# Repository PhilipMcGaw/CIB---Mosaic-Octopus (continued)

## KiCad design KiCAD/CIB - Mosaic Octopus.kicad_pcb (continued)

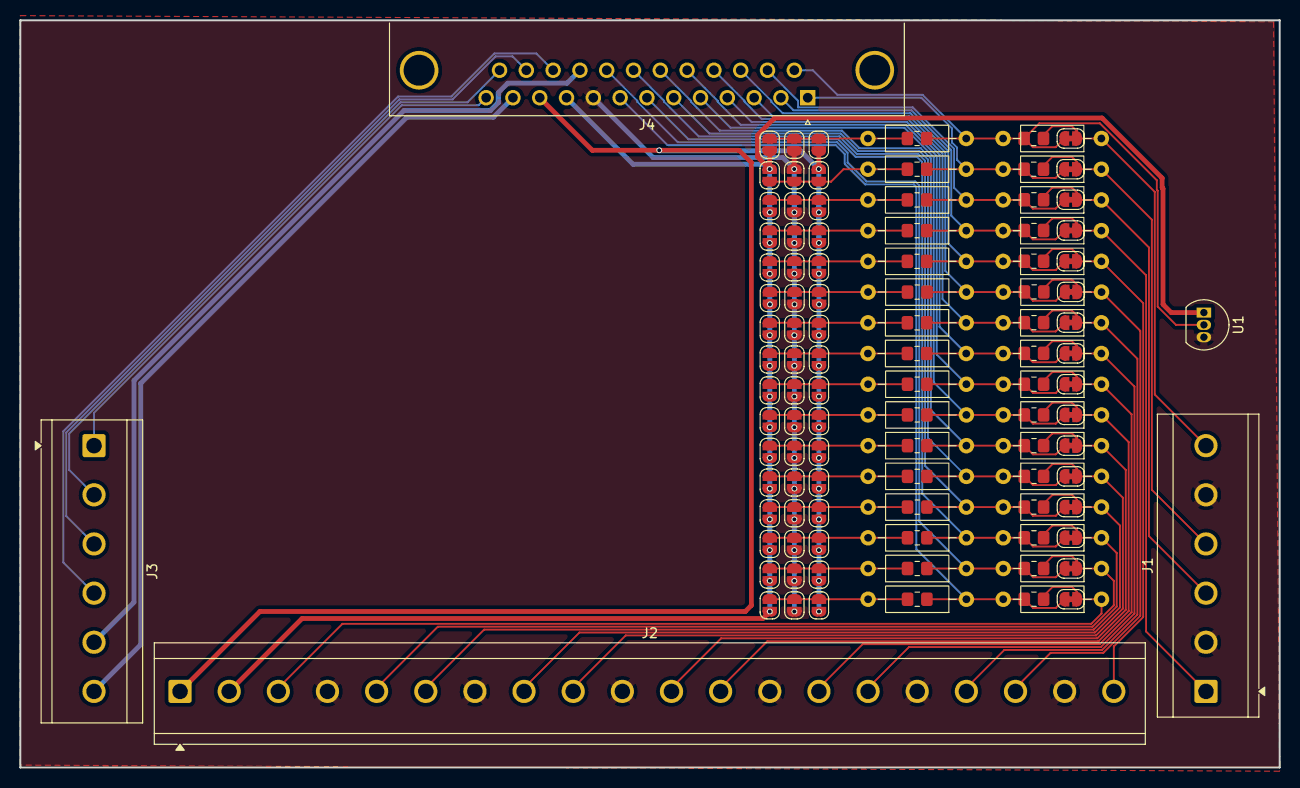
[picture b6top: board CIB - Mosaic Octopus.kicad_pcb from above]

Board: 2 copper layers, 130.2 x 77.2 mm, 133 parts (0 on the bottom side), 57 nets.

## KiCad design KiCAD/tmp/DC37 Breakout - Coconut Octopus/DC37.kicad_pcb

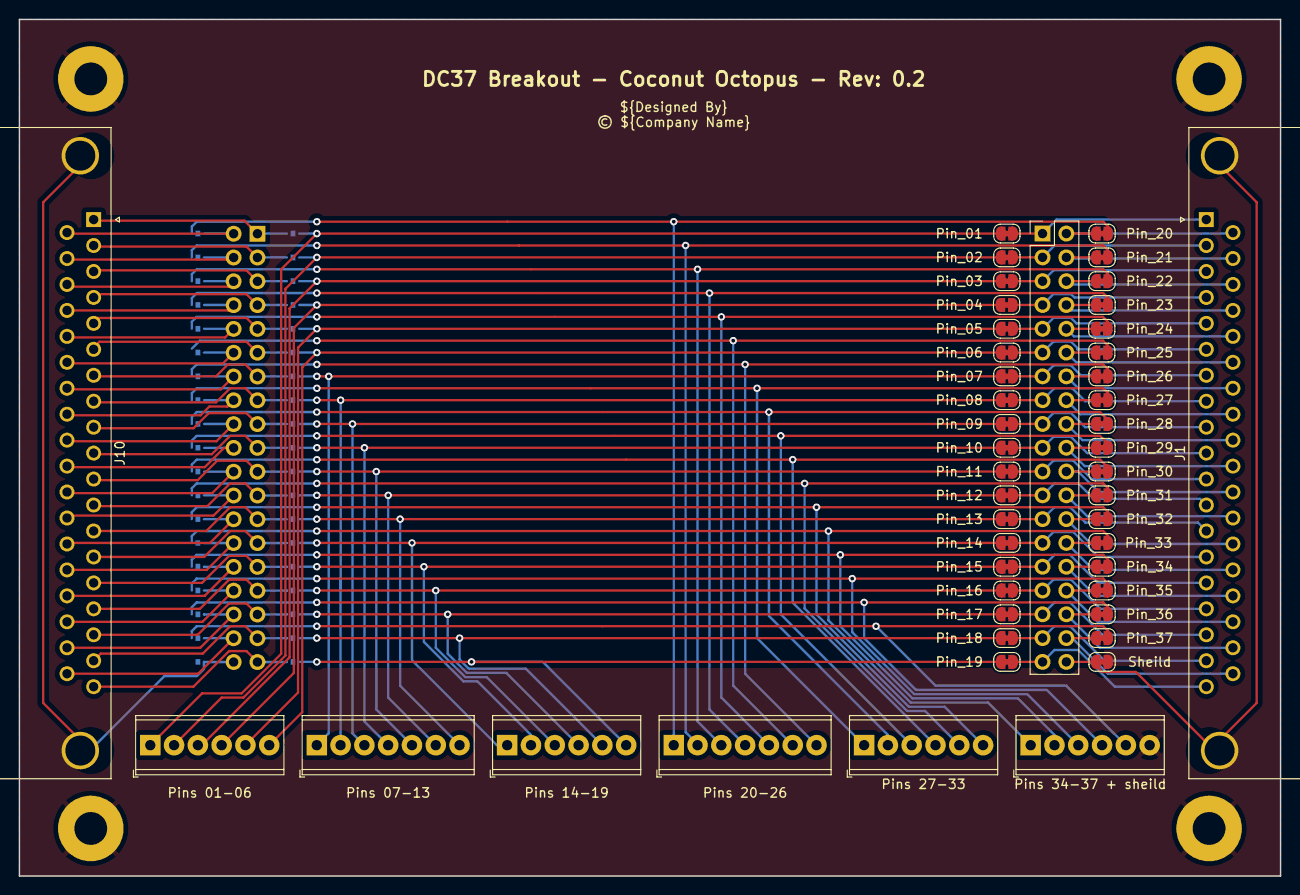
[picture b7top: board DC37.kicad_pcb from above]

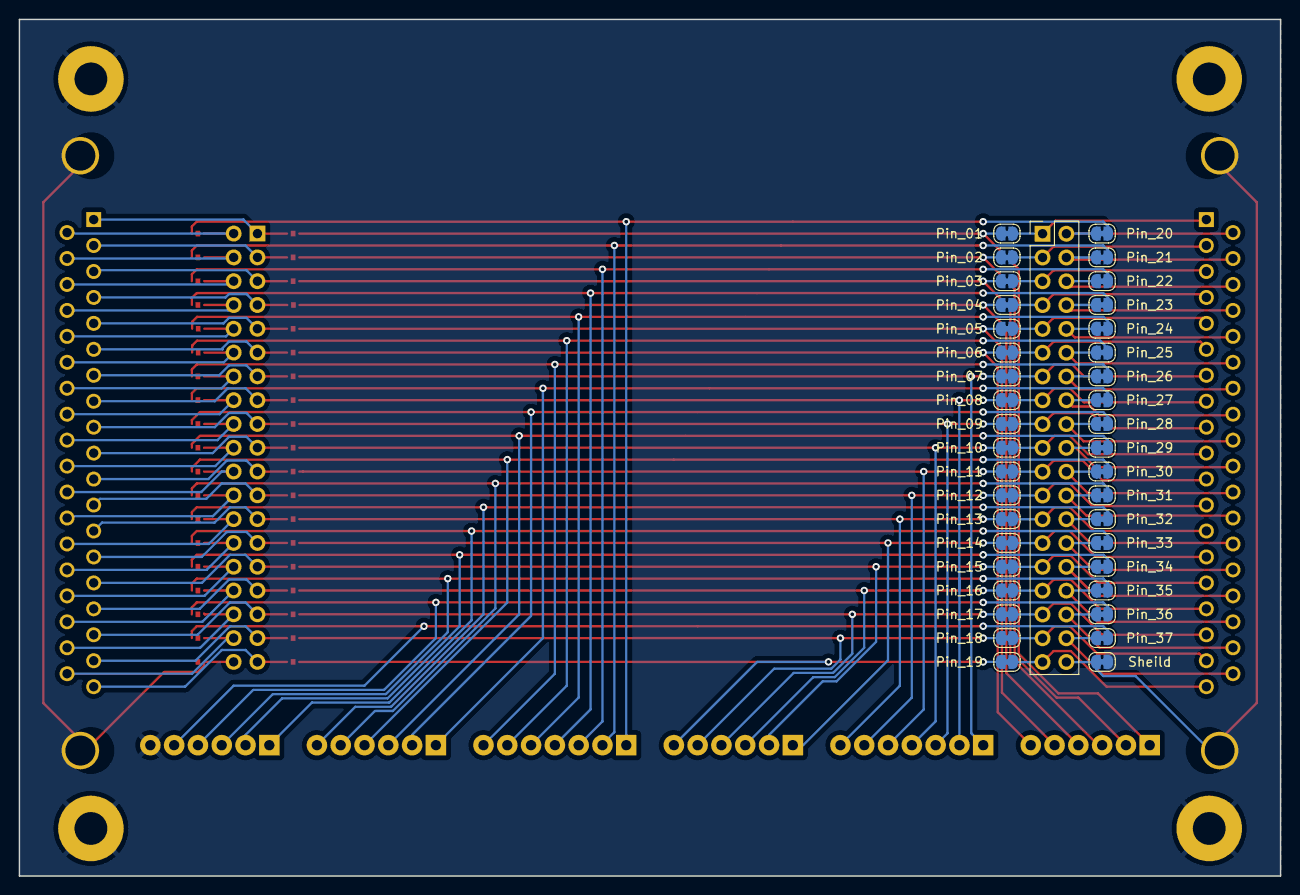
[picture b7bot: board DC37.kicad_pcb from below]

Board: 2 copper layers, 134.6 x 91.4 mm, 90 parts (39 on the bottom side), 114 nets.

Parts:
H1, H2, H3, H4: MountingHole; MountingHole_3.5mm_Pad
J1: DC37; DSUB-37_Female_Horizontal_P2.77x2.84mm_EdgePinOffset7.70mm_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
J2, J9: Pin Header; PinHeader_2x19_P2.54mm_Vertical
J3: Pins 01-06; TerminalBlock_Phoenix_MPT-0,5-6-2.54_1x06_P2.54mm_Horizontal
J4: Pins 07-13; TerminalBlock_Phoenix_MPT-0,5-7-2.54_1x07_P2.54mm_Horizontal
J5: Pins 14-19; TerminalBlock_Phoenix_MPT-0,5-6-2.54_1x06_P2.54mm_Horizontal
J6: Pins 20-26; TerminalBlock_Phoenix_MPT-0,5-7-2.54_1x07_P2.54mm_Horizontal
J7: Pins 27-33; TerminalBlock_Phoenix_MPT-0,5-6-2.54_1x06_P2.54mm_Horizontal
J8: Pins 34-37 + sheild; TerminalBlock_Phoenix_MPT-0,5-6-2.54_1x06_P2.54mm_Horizontal
J10: DC37; DSUB-37_Male_Horizontal_P2.77x2.84mm_EdgePinOffset7.70mm_Ho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
JP1, JP39: Pin_01; SolderJumper-2_P1.3mm_Bridged_RoundedPad1.0x1.5mm
JP2, JP40: Pin_20; SolderJumper-2_P1.3mm_Bridged_RoundedPad1.0x1.5mm
JP3, JP41: Pin_02; SolderJumper-2_P1.3mm_Bridged_RoundedPad1.0x1.5mm
JP4, JP42: Pin_21; SolderJumper-2_P1.3mm_Bridged_RoundedPad1.0x1.5mm
JP5, JP43: Pin_03; SolderJumper-2_P1.3mm_Bridged_RoundedPad1.0x1.5mm
JP6, JP44: Pin_22; SolderJumper-2_P1.3mm_Bridged_RoundedPad1.0x1.5mm
JP7, JP45: Pin_04; SolderJumper-2_P1.3mm_Bridged_RoundedPad1.0x1.5mm
JP8, JP46: Pin_23; SolderJumper-2_P1.3mm_Bridged_RoundedPad1.0x1.5mm
JP9, JP47: Pin_05; SolderJumper-2_P1.3mm_Bridged_RoundedPad1.0x1.5mm
JP10, JP48: Pin_24; SolderJumper-2_P1.3mm_Bridged_RoundedPad1.0x1.5mm
JP11, JP49: Pin_06; SolderJumper-2_P1.3mm_Bridged_RoundedPad1.0x1.5mm
JP12, JP50: Pin_25; SolderJumper-2_P1.3mm_Bridged_RoundedPad1.0x1.5mm
JP13, JP51: Pin_07; SolderJumper-2_P1.3mm_Bridged_RoundedPad1.0x1.5mm
JP14, JP52: Pin_26; SolderJumper-2_P1.3mm_Bridged_RoundedPad1.0x1.5mm
JP15, JP53: Pin_08; SolderJumper-2_P1.3mm_Bridged_RoundedPad1.0x1.5mm
JP16, JP54: Pin_27; SolderJumper-2_P1.3mm_Bridged_RoundedPad1.0x1.5mm
JP17, JP55: Pin_09; SolderJumper-2_P1.3mm_Bridged_RoundedPad1.0x1.5mm
JP18, JP56: Pin_28; SolderJumper-2_P1.3mm_Bridged_RoundedPad1.0x1.5mm
JP19, JP57: Pin_10; SolderJumper-2_P1.3mm_Bridged_RoundedPad1.0x1.5mm
JP20, JP58: Pin_29; SolderJumper-2_P1.3mm_Bridged_RoundedPad1.0x1.5mm
JP21, JP59: Pin_11; SolderJumper-2_P1.3mm_Bridged_RoundedPad1.0x1.5mm
JP22, JP60: Pin_30; SolderJumper-2_P1.3mm_Bridged_RoundedPad1.0x1.5mm
JP23, JP61: Pin_12; SolderJumper-2_P1.3mm_Bridged_RoundedPad1.0x1.5mm
JP24, JP62: Pin_31; SolderJumper-2_P1.3mm_Bridged_RoundedPad1.0x1.5mm
JP25, JP63: Pin_13; SolderJumper-2_P1.3mm_Bridged_RoundedPad1.0x1.5mm
JP26, JP64: Pin_32; SolderJumper-2_P1.3mm_Bridged_RoundedPad1.0x1.5mm
JP27, JP65: Pin_14; SolderJumper-2_P1.3mm_Bridged_RoundedPad1.0x1.5mm
JP28, JP66: Pin_33; SolderJumper-2_P1.3mm_Bridged_RoundedPad1.0x1.5mm
JP29, JP67: Pin_15; SolderJumper-2_P1.3mm_Bridged_RoundedPad1.0x1.5mm
JP30, JP68: Pin_34; SolderJumper-2_P1.3mm_Bridged_RoundedPad1.0x1.5mm
JP31, JP69: Pin_16; SolderJumper-2_P1.3mm_Bridged_RoundedPad1.0x1.5mm
JP32, JP70: Pin_35; SolderJumper-2_P1.3mm_Bridged_RoundedPad1.0x1.5mm
JP33, JP71: Pin_17; SolderJumper-2_P1.3mm_Bridged_RoundedPad1.0x1.5mm
JP34, JP72: Pin_36; SolderJumper-2_P1.3mm_Bridged_RoundedPad1.0x1.5mm
JP35, JP73: Pin_18; SolderJumper-2_P1.3mm_Bridged_RoundedPad1.0x1.5mm
JP36, JP74: Pin_37; SolderJumper-2_P1.3mm_Bridged_RoundedPad1.0x1.5mm
JP37, JP75: Pin_19; SolderJumper-2_P1.3mm_Bridged_RoundedPad1.0x1.5mm
JP38, JP76: Sheild; SolderJumper-2_P1.3mm_Bridged_RoundedPad1.0x1.5mm

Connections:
/Pin_01: J3.1, JP1.2 (B), JP39.1 (A)
/Pin_02: J3.2, JP3.2 (B), JP41.1 (A)
/Pin_03: J3.3, JP5.2 (B), JP43.1 (A)
/Pin_04: J3.4, JP7.2 (B), JP45.1 (A)
/Pin_05: J3.5, JP9.2 (B), JP47.1 (A)
/Pin_06: J3.6, JP11.2 (B), JP49.1 (A)
/Pin_07: J4.1, JP13.2 (B), JP51.1 (A)
/Pin_08: J4.2, JP15.2 (B), JP53.1 (A)
/Pin_09: J4.3, JP17.2 (B), JP55.1 (A)
/Pin_10: J4.4, JP19.2 (B), JP57.1 (A)
/Pin_11: J4.5, JP21.2 (B), JP59.1 (A)
/Pin_12: J4.6, JP23.2 (B), JP61.1 (A)
/Pin_13: J4.7, JP25.2 (B), JP63.1 (A)
/Pin_14: J5.1, JP27.2 (B), JP65.1 (A)
/Pin_15: J5.2, JP29.2 (B), JP67.1 (A)
/Pin_16: J5.3, JP31.2 (B), JP69.1 (A)
/Pin_17: J5.4, JP33.2 (B), JP71.1 (A)
/Pin_18: J5.5, JP35.2 (B), JP73.1 (A)
/Pin_19: J5.6, JP37.2 (B), JP75.1 (A)
/Pin_20: J6.1, JP2.2 (B), JP40.1 (A)
/Pin_21: J6.2, JP4.2 (B), JP42.1 (A)
/Pin_22: J6.3, JP6.2 (B), JP44.1 (A)
/Pin_23: J6.4, JP8.2 (B), JP46.1 (A)
/Pin_24: J6.5, JP10.2 (B), JP48.1 (A)
/Pin_25: J6.6, JP12.2 (B), JP50.1 (A)
/Pin_26: J6.7, JP14.2 (B), JP52.1 (A)
/Pin_27: J7.1, JP16.2 (B), JP54.1 (A)
/Pin_28: J7.2, JP18.2 (B), JP56.1 (A)
/Pin_29: J7.3, JP20.2 (B), JP58.1 (A)
/Pin_30: J7.4, JP22.2 (B), JP60.1 (A)
/Pin_31: J7.5, JP24.2 (B), JP62.1 (A)
/Pin_32: J7.6, JP26.2 (B), JP64.1 (A)
/Pin_33: J8.1, JP28.2 (B), JP66.1 (A)
/Pin_34: J8.2, JP30.2 (B), JP68.1 (A)
/Pin_35: J8.3, JP32.2 (B), JP70.1 (A)
/Pin_36: J8.4, JP34.2 (B), JP72.1 (A)
/Pin_37: J8.5, JP36.2 (B), JP74.1 (A)
GND: H1.1, H2.1, H3.1, H4.1, J8.6, JP38.2 (B), JP76.1 (A)
unnamed: J1.0 (PAD), J2.38, JP38.1 (A)
unnamed: J1.1, J2.1, JP1.1 (A)
unnamed: J1.20, J2.2, JP2.1 (A)
unnamed: J1.2, J2.3, JP3.1 (A)
unnamed: J1.21, J2.4, JP4.1 (A)
unnamed: J1.3, J2.5, JP5.1 (A)
unnamed: J1.22, J2.6, JP6.1 (A)
unnamed: J1.4, J2.7, JP7.1 (A)
unnamed: J1.23, J2.8, JP8.1 (A)
unnamed: J1.5, J2.9, JP9.1 (A)
unnamed: J1.24, J2.10, JP10.1 (A)
unnamed: J1.6, J2.11, JP11.1 (A)
unnamed: J1.25, J2.12, JP12.1 (A)
unnamed: J1.7, J2.13, JP13.1 (A)
unnamed: J1.26, J2.14, JP14.1 (A)
unnamed: J1.8, J2.15, JP15.1 (A)
unnamed: J1.27, J2.16, JP16.1 (A)
unnamed: J1.9, J2.17, JP17.1 (A)
unnamed: J1.28, J2.18, JP18.1 (A)
unnamed: J1.10, J2.19, JP19.1 (A)
unnamed: J1.29, J2.20, JP20.1 (A)
unnamed: J1.11, J2.21, JP21.1 (A)
unnamed: J1.30, J2.22, JP22.1 (A)
unnamed: J1.12, J2.23, JP23.1 (A)
unnamed: J1.31, J2.24, JP24.1 (A)
unnamed: J1.13, J2.25, JP25.1 (A)
unnamed: J1.32, J2.26, JP26.1 (A)
unnamed: J1.14, J2.27, JP27.1 (A)
unnamed: J1.33, J2.28, JP28.1 (A)
unnamed: J1.15, J2.29, JP29.1 (A)
unnamed: J1.34, J2.30, JP30.1 (A)
unnamed: J1.16, J2.31, JP31.1 (A)
unnamed: J1.35, J2.32, JP32.1 (A)
unnamed: J1.17, J2.33, JP33.1 (A)
unnamed: J1.36, J2.34, JP34.1 (A)
unnamed: J1.18, J2.35, JP35.1 (A)
unnamed: J1.37, J2.36, JP36.1 (A)
unnamed: J1.19, J2.37, JP37.1 (A)
unnamed: J9.1, J10.1, JP39.2 (B)
unnamed: J9.2, J10.20, JP40.2 (B)
unnamed: J9.3, J10.2, JP41.2 (B)
unnamed: J9.4, J10.21, JP42.2 (B)
unnamed: J9.5, J10.3, JP43.2 (B)
unnamed: J9.6, J10.22, JP44.2 (B)
unnamed: J9.7, J10.4, JP45.2 (B)
unnamed: J9.8, J10.23, JP46.2 (B)
unnamed: J9.9, J10.5, JP47.2 (B)
unnamed: J9.10, J10.24, JP48.2 (B)
unnamed: J9.11, J10.6, JP49.2 (B)
unnamed: J9.12, J10.25, JP50.2 (B)
unnamed: J9.13, J10.7, JP51.2 (B)
unnamed: J9.14, J10.26, JP52.2 (B)
unnamed: J9.15, J10.8, JP53.2 (B)
unnamed: J9.16, J10.27, JP54.2 (B)
unnamed: J9.17, J10.9, JP55.2 (B)
unnamed: J9.18, J10.28, JP56.2 (B)
unnamed: J9.19, J10.10, JP57.2 (B)
unnamed: J9.20, J10.29, JP58.2 (B)
unnamed: J9.21, J10.11, JP59.2 (B)
unnamed: J9.22, J10.30, JP60.2 (B)
unnamed: J9.23, J10.12, JP61.2 (B)
unnamed: J9.24, J10.31, JP62.2 (B)
unnamed: J9.25, J10.13, JP63.2 (B)
unnamed: J9.26, J10.32, JP64.2 (B)
unnamed: J9.27, J10.14, JP65.2 (B)
unnamed: J9.28, J10.33, JP66.2 (B)
unnamed: J9.29, J10.15, JP67.2 (B)
unnamed: J9.30, J10.34, JP68.2 (B)
unnamed: J9.31, J10.16, JP69.2 (B)
unnamed: J9.32, J10.35, JP70.2 (B)
unnamed: J9.33, J10.17, JP71.2 (B)
unnamed: J9.34, J10.36, JP72.2 (B)
unnamed: J9.35, J10.18, JP73.2 (B)
unnamed: J9.36, J10.37, JP74.2 (B)
unnamed: J9.37, J10.19, JP75.2 (B)
unnamed: J9.38, J10.0 (PAD), JP76.2 (B)

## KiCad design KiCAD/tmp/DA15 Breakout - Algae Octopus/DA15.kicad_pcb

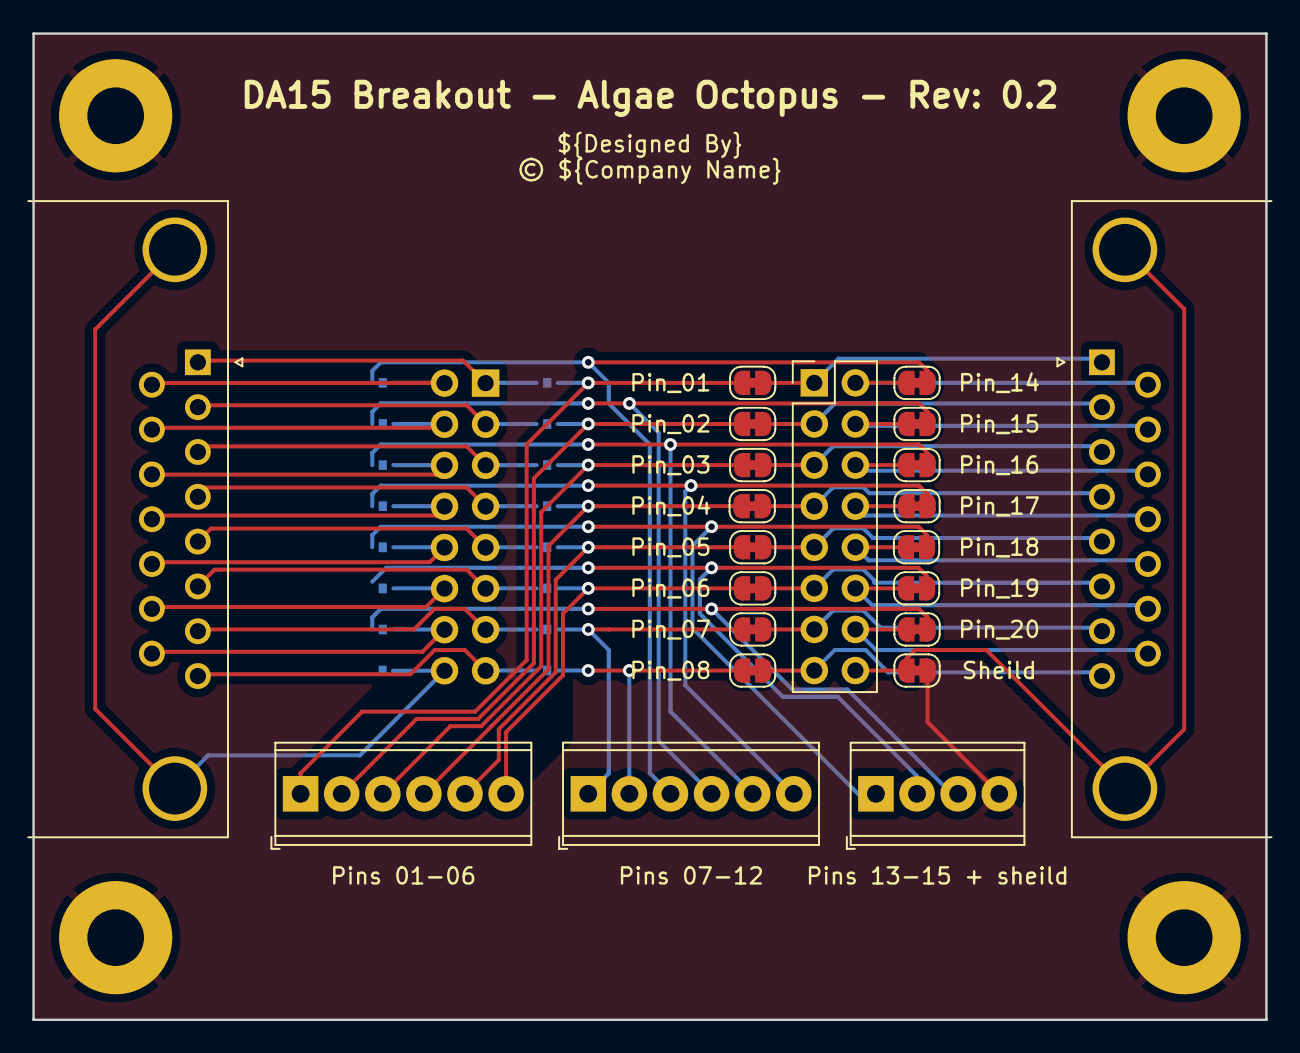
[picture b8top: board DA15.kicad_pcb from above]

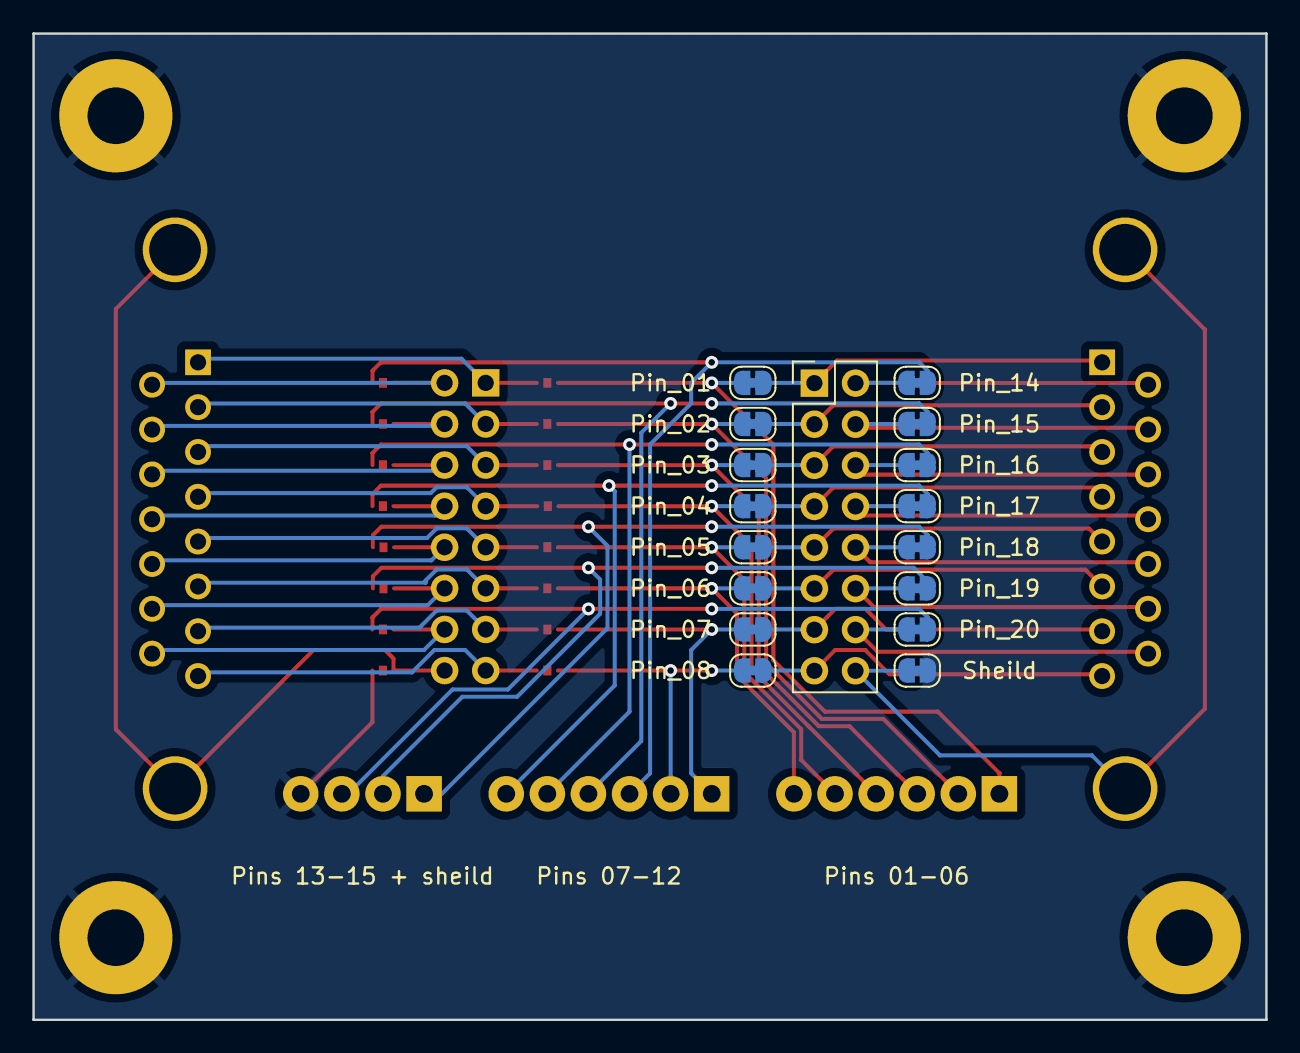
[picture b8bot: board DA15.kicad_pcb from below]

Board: 2 copper layers, 76.2 x 61.0 mm, 43 parts (17 on the bottom side), 48 nets.

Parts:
H1, H2, H3, H4: MountingHole; MountingHole_3.5mm_Pad
J1: DA15; DSUB-15_Female_Horizontal_P2.77x2.84mm_EdgePinOffset7.70mm_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
J2: DA15; DSUB-15_Male_Horizontal_P2.77x2.84mm_EdgePinOffset7.70mm_Ho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
J3: Pins 01-06; TerminalBlock_Phoenix_MPT-0,5-6-2.54_1x06_P2.54mm_Horizontal
J4: Pins 07-12; TerminalBlock_Phoenix_MPT-0,5-6-2.54_1x06_P2.54mm_Horizontal
J5: Pins 13-15 + sheild; TerminalBlock_Phoenix_MPT-0,5-4-2.54_1x04_P2.54mm_Horizontal
J6, J7: Pin Header; PinHeader_2x08_P2.54mm_Vertical
JP1, JP5: Pin_01; SolderJumper-2_P1.3mm_Bridged_RoundedPad1.0x1.5mm
JP2, JP7: Pin_14; SolderJumper-2_P1.3mm_Bridged_RoundedPad1.0x1.5mm
JP3, JP52: Sheild; SolderJumper-2_P1.3mm_Bridged_RoundedPad1.0x1.5mm
JP4, JP9: Pin_02; SolderJumper-2_P1.3mm_Bridged_RoundedPad1.0x1.5mm
JP6, JP11: Pin_15; SolderJumper-2_P1.3mm_Bridged_RoundedPad1.0x1.5mm
JP8, JP13: Pin_03; SolderJumper-2_P1.3mm_Bridged_RoundedPad1.0x1.5mm
JP10, JP15: Pin_16; SolderJumper-2_P1.3mm_Bridged_RoundedPad1.0x1.5mm
JP12, JP17: Pin_04; SolderJumper-2_P1.3mm_Bridged_RoundedPad1.0x1.5mm
JP14, JP19: Pin_17; SolderJumper-2_P1.3mm_Bridged_RoundedPad1.0x1.5mm
JP16, JP21: Pin_05; SolderJumper-2_P1.3mm_Bridged_RoundedPad1.0x1.5mm
JP18, JP22: Pin_18; SolderJumper-2_P1.3mm_Bridged_RoundedPad1.0x1.5mm
JP20, JP23: Pin_06; SolderJumper-2_P1.3mm_Bridged_RoundedPad1.0x1.5mm
JP24, JP30: Pin_19; SolderJumper-2_P1.3mm_Bridged_RoundedPad1.0x1.5mm
JP25, JP32: Pin_07; SolderJumper-2_P1.3mm_Bridged_RoundedPad1.0x1.5mm
JP26, JP34: Pin_20; SolderJumper-2_P1.3mm_Bridged_RoundedPad1.0x1.5mm
JP27, JP35: Pin_08; SolderJumper-2_P1.3mm_Bridged_RoundedPad1.0x1.5mm

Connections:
/Pin_01: J3.1, JP1.2 (B), JP5.1 (A)
/Pin_02: J3.2, JP4.2 (B), JP9.1 (A)
/Pin_03: J3.3, JP8.2 (B), JP13.1 (A)
/Pin_04: J3.4, JP12.2 (B), JP17.1 (A)
/Pin_05: J3.5, JP16.2 (B), JP21.1 (A)
/Pin_06: J3.6, JP20.2 (B), JP23.1 (A)
/Pin_07: J4.1, JP25.1 (A), JP32.2 (B)
/Pin_08: J4.2, JP27.1 (A), JP35.2 (B)
/Pin_09: J4.3, JP2.2 (B), JP7.1 (A)
/Pin_10: J4.4, JP6.2 (B), JP11.1 (A)
/Pin_11: J4.5, JP10.2 (B), JP15.1 (A)
/Pin_12: J4.6, JP14.2 (B), JP19.1 (A)
/Pin_13: J5.1, JP18.2 (B), JP22.1 (A)
/Pin_14: J5.2, JP24.1 (A), JP30.2 (B)
/Pin_15: J5.3, JP26.1 (A), JP34.2 (B)
GND: H1.1, H2.1, H3.1, H4.1, J5.4, JP3.1 (A), JP52.2 (B)
unnamed: J1.9, J6.2, JP2.1 (A)
unnamed: J1.10, J6.4, JP6.1 (A)
unnamed: J1.12, J6.8, JP14.1 (A)
unnamed: J1.13, J6.10, JP18.1 (A)
unnamed: J1.14, J6.12, JP30.1 (A)
unnamed: J1.15, J6.14, JP34.1 (A)
unnamed: J1.11 (P111), J6.6, JP10.1 (A)
unnamed: J1.0 (PAD), J6.16, JP52.1 (A)
unnamed: J2.9, J7.2, JP7.2 (B)
unnamed: J2.10, J7.4, JP11.2 (B)
unnamed: J2.12, J7.8, JP19.2 (B)
unnamed: J2.13, J7.10, JP22.2 (B)
unnamed: J2.14, J7.12, JP24.2 (B)
unnamed: J2.15, J7.14, JP26.2 (B)
unnamed: J2.11 (P111), J7.6, JP15.2 (B)
unnamed: J2.0 (PAD), J7.16, JP3.2 (B)
unnamed: J1.1, J6.1, JP1.1 (A)
unnamed: J1.2, J6.3, JP4.1 (A)
unnamed: J1.3, J6.5, JP8.1 (A)
unnamed: J1.4, J6.7, JP12.1 (A)
unnamed: J1.5, J6.9, JP16.1 (A)
unnamed: J1.6, J6.11, JP20.1 (A)
unnamed: J1.7, J6.13, JP32.1 (A)
unnamed: J1.8, J6.15, JP35.1 (A)
unnamed: J2.1, J7.1, JP5.2 (B)
unnamed: J2.2, J7.3, JP9.2 (B)
unnamed: J2.3, J7.5, JP13.2 (B)
unnamed: J2.4, J7.7, JP17.2 (B)
unnamed: J2.5, J7.9, JP21.2 (B)
unnamed: J2.6, J7.11, JP23.2 (B)
unnamed: J2.7, J7.13, JP25.2 (B)
unnamed: J2.8, J7.15, JP27.2 (B)
